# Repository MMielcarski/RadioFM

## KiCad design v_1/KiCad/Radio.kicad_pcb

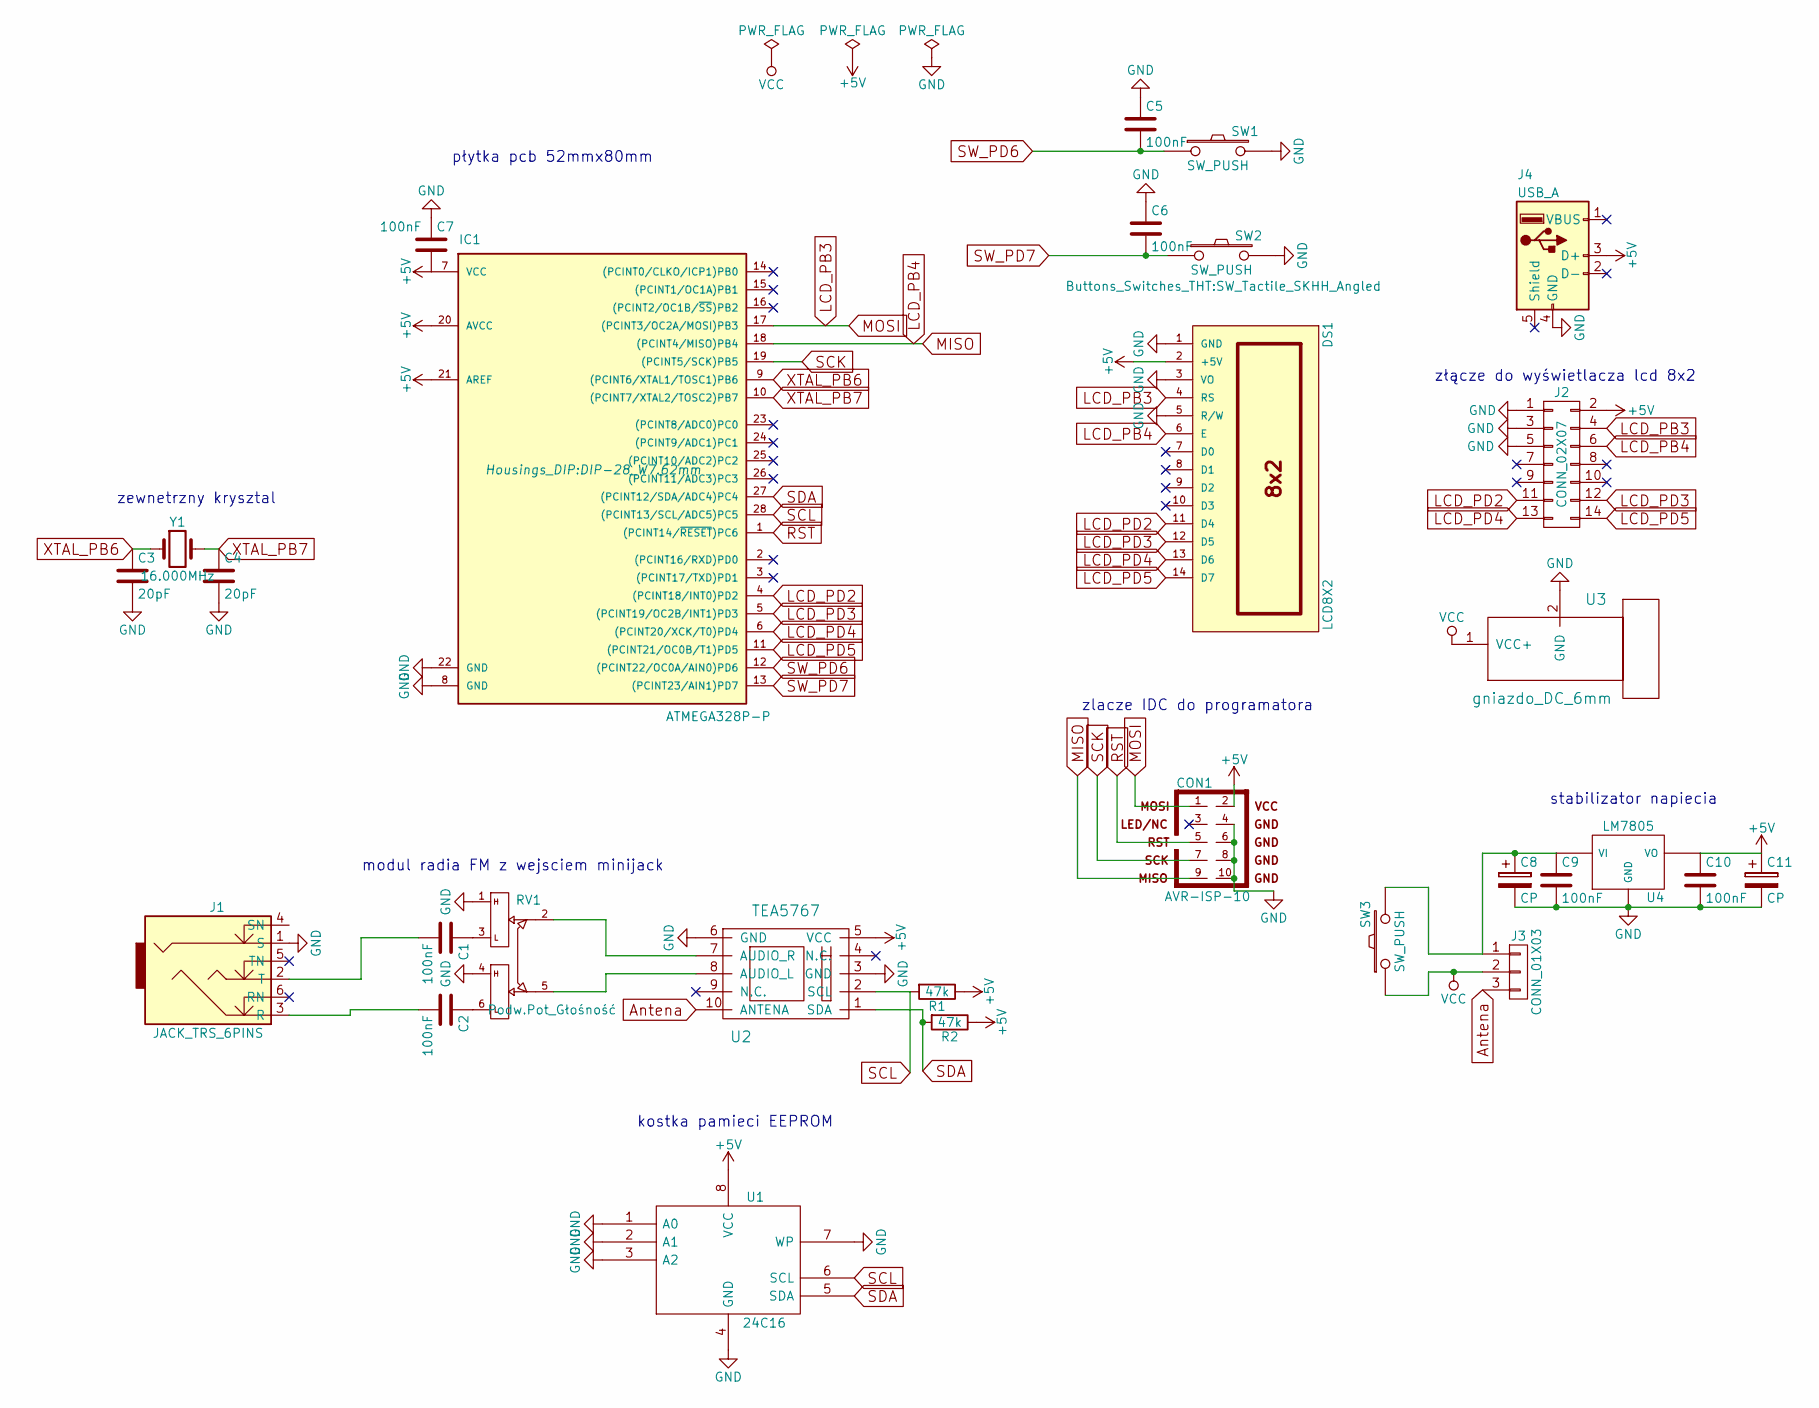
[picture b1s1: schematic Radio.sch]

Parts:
C1, C2, C5, C6, C7, C9, C10: 100nF; CP_Radial_Tantal_D4.5mm_P2.50mm
C3, C4: 20pF; CP_Radial_Tantal_D4.5mm_P2.50mm
C8, C11: CP; CP_Radial_D5.0mm_P2.50mm
CON1: AVR-ISP-10; IDC_Header_Straight_10pins
DS1: LCD8X2
IC1: ATMEGA328P-P; DIP-28_W7.62mm
J1: JACK_TRS_6PINS; Tayda_3.5mm_stereo_TRS_jack_A-853
J2: CONN_02X07; Pin_Header_Straight_2x07_Pitch2.54mm
J3: CONN_01X03; Pin_Header_Straight_1x03_Pitch2.54mm
J4: USB_A
R1, R2: 47k; R_Axial_DIN0204_L3.6mm_D1.6mm_P7.62mm_Horizontal
RV1: Podw.Pot_Głośność; Pin_Header_Straight_2x03_Pitch2.54mm
SW1, SW2, SW3: SW_PUSH; SW_Tactile_SKHH_Angled
U1: 24C16; DIP-8_W7.62mm
U2: TEA5767
U3: gniazdo_DC_6mm
U4: LM7805
Y1: 16.000MHz; Crystal_HC18-U_Vertical

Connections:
+5V: C7.2, C10.1, C11.1, CON1.2, DS1.2 (+5V), IC1.7 (VCC), IC1.20 (AVCC), IC1.21 (AREF), J2.2, J4.3 (D+), R1.1, R2.1, U1.8 (VCC), U2.5 (VCC), U4.3 (VO)
Antena: J3.3, U2.10 (ANTENA)
GND: C3.2, C4.2, C5.1, C6.1, C7.1, C8.2, C9.2, C10.2, C11.2, CON1.4, CON1.6, CON1.8, CON1.10, DS1.1 (GND), DS1.3 (VO), DS1.5 (R/W), IC1.8 (GND), IC1.22 (GND), J1.1 (S), J2.1, J2.3, J2.5, J4.4 (GND), RV1.1, RV1.4, SW1.2, SW2.2, U1.1 (A0), U1.2 (A1), U1.3 (A2), U1.4 (GND), U1.7 (WP), U2.3 (GND), U2.6 (GND), U3.2 (GND), U4.2 (GND)
LCD_PB3: CON1.1, DS1.4 (RS), IC1.17 ((PCINT3/OC2A/MOSI)PB3), J2.4
LCD_PB4: CON1.9, DS1.6 (E), IC1.18 ((PCINT4/MISO)PB4), J2.6
LCD_PD2: DS1.11 (D4), IC1.4 ((PCINT18/INT0)PD2), J2.11
LCD_PD3: DS1.12 (D5), IC1.5 ((PCINT19/OC2B/INT1)PD3), J2.12
LCD_PD4: DS1.13 (D6), IC1.6 ((PCINT20/XCK/T0)PD4), J2.13
LCD_PD5: DS1.14 (D7), IC1.11 ((PCINT21/OC0B/T1)PD5), J2.14
unnamed: C1.1, RV1.3
unnamed: C1.2, J1.2 (T)
unnamed: C2.1, RV1.6
unnamed: C2.2, J1.3 (R)
unnamed: C8.1, C9.1, J3.1, SW3.2, U4.1 (VI)
unnamed: RV1.2, U2.7 (AUDIO_R)
unnamed: RV1.5, U2.8 (AUDIO_L)
RST: CON1.5, IC1.1 ((PCINT14/~RESET~)PC6)
SCK: CON1.7, IC1.19 ((PCINT5/SCK)PB5)
SCL: IC1.28 ((PCINT13/SCL/ADC5)PC5), R1.2, U1.6 (SCL), U2.2 (SCL)
SDA: IC1.27 ((PCINT12/SDA/ADC4)PC4), R2.2, U1.5 (SDA), U2.1 (SDA)
SW_PD6: C5.2, IC1.12 ((PCINT22/OC0A/AIN0)PD6), SW1.1
SW_PD7: C6.2, IC1.13 ((PCINT23/AIN1)PD7), SW2.1
VCC: J3.2, SW3.1, U3.1 (VCC+)
XTAL_PB6: C3.1, IC1.9 ((PCINT6/XTAL1/TOSC1)PB6), Y1.1
XTAL_PB7: C4.1, IC1.10 ((PCINT7/XTAL2/TOSC2)PB7), Y1.2

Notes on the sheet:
płytka pcb 52mmx80mm
złącze do wyświetlacza lcd 8x2
stabilizator napiecia
zlacze IDC do programatora
kostka pamieci EEPROM
modul radia FM z wejsciem minijack
zewnetrzny krysztal

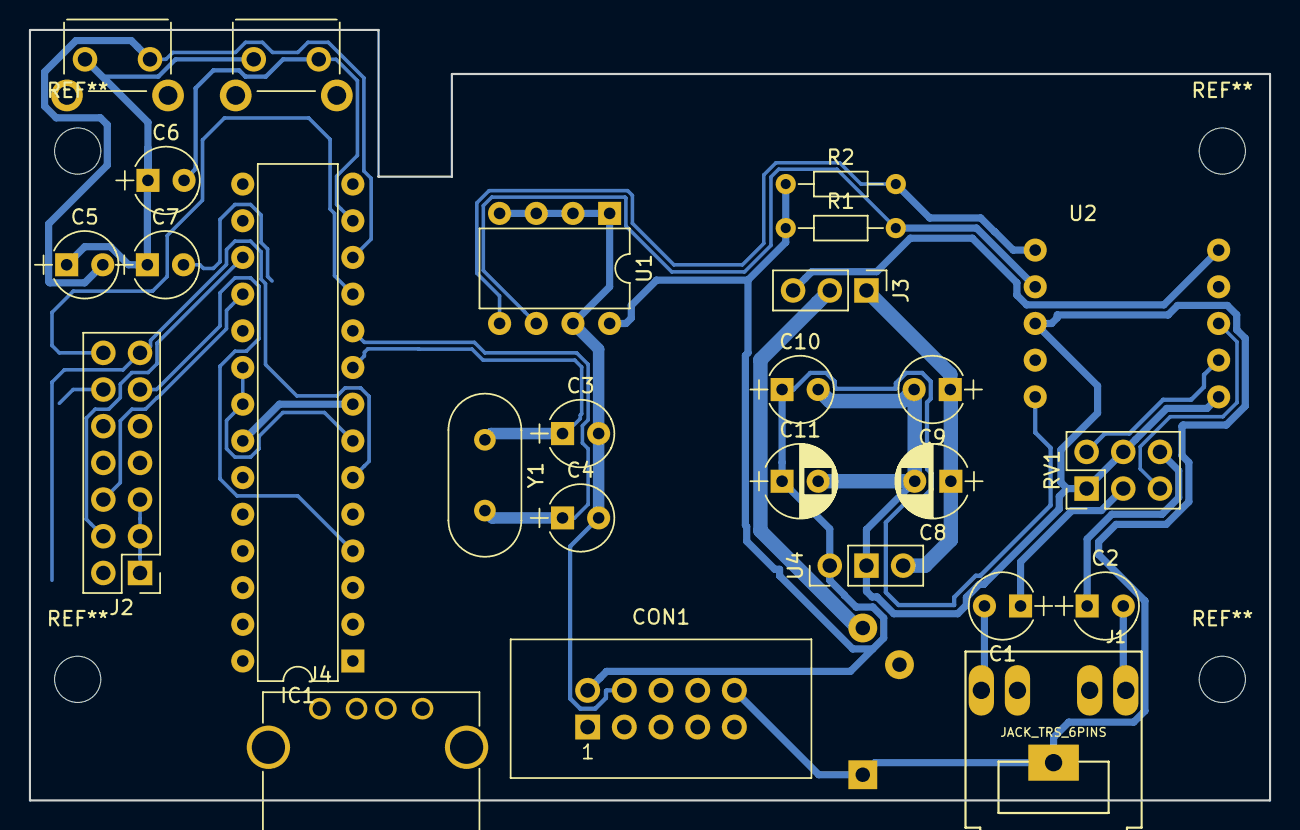
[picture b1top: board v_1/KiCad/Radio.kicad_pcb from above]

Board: 2 copper layers, 85.9 x 53.3 mm, 27 parts (0 on the bottom side), 25 nets.

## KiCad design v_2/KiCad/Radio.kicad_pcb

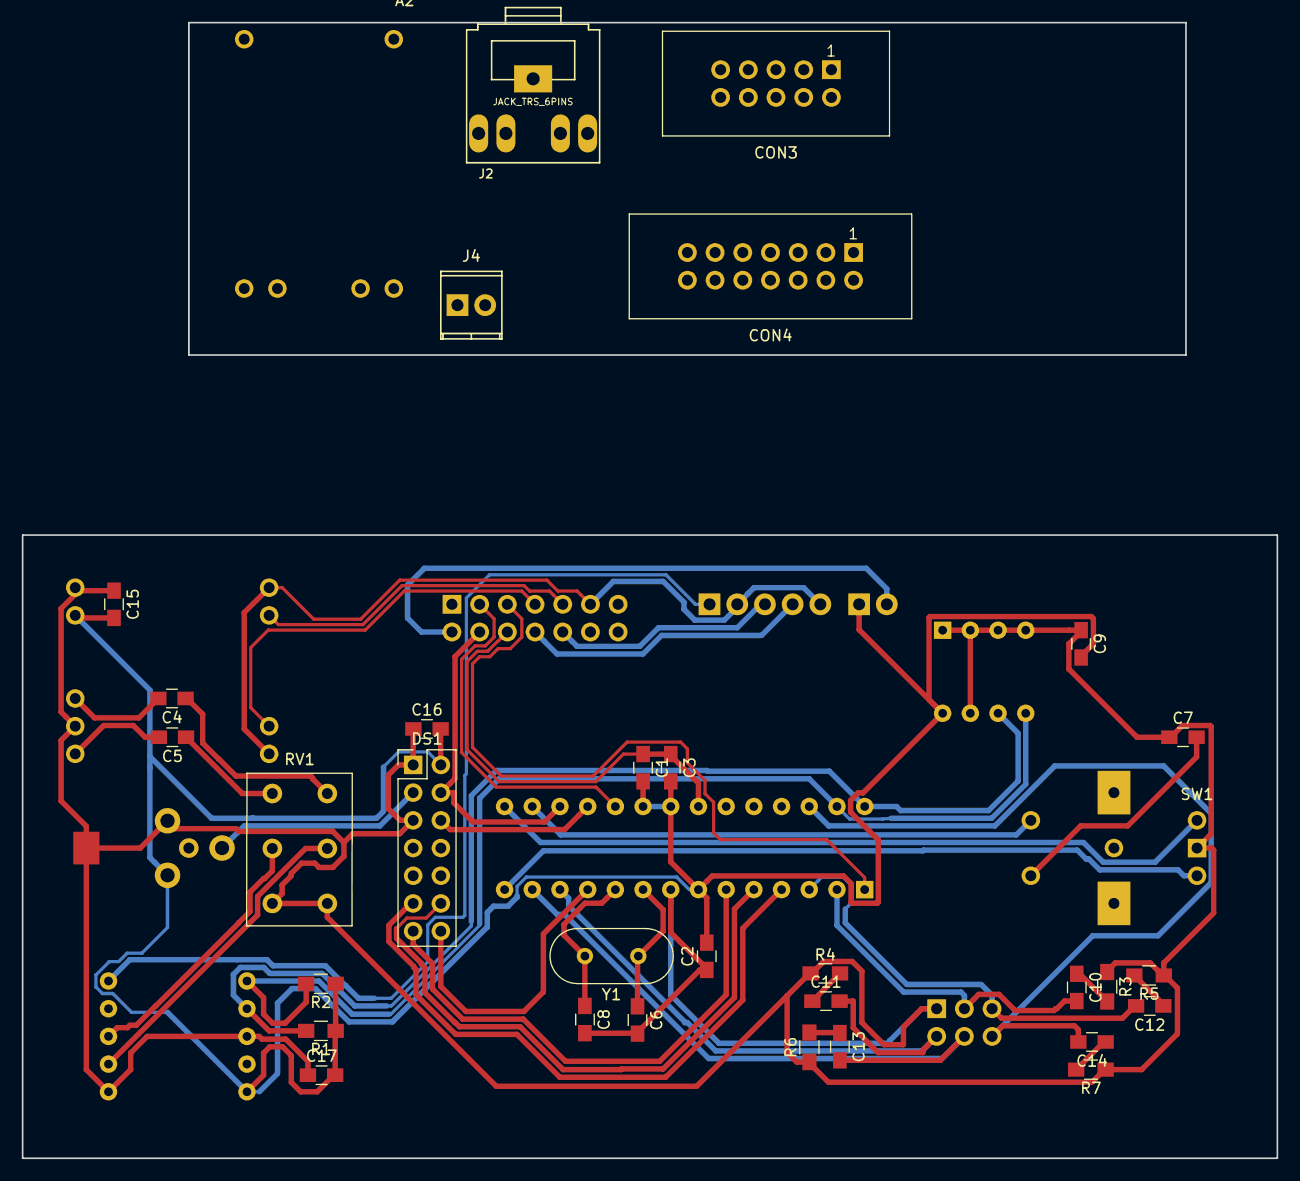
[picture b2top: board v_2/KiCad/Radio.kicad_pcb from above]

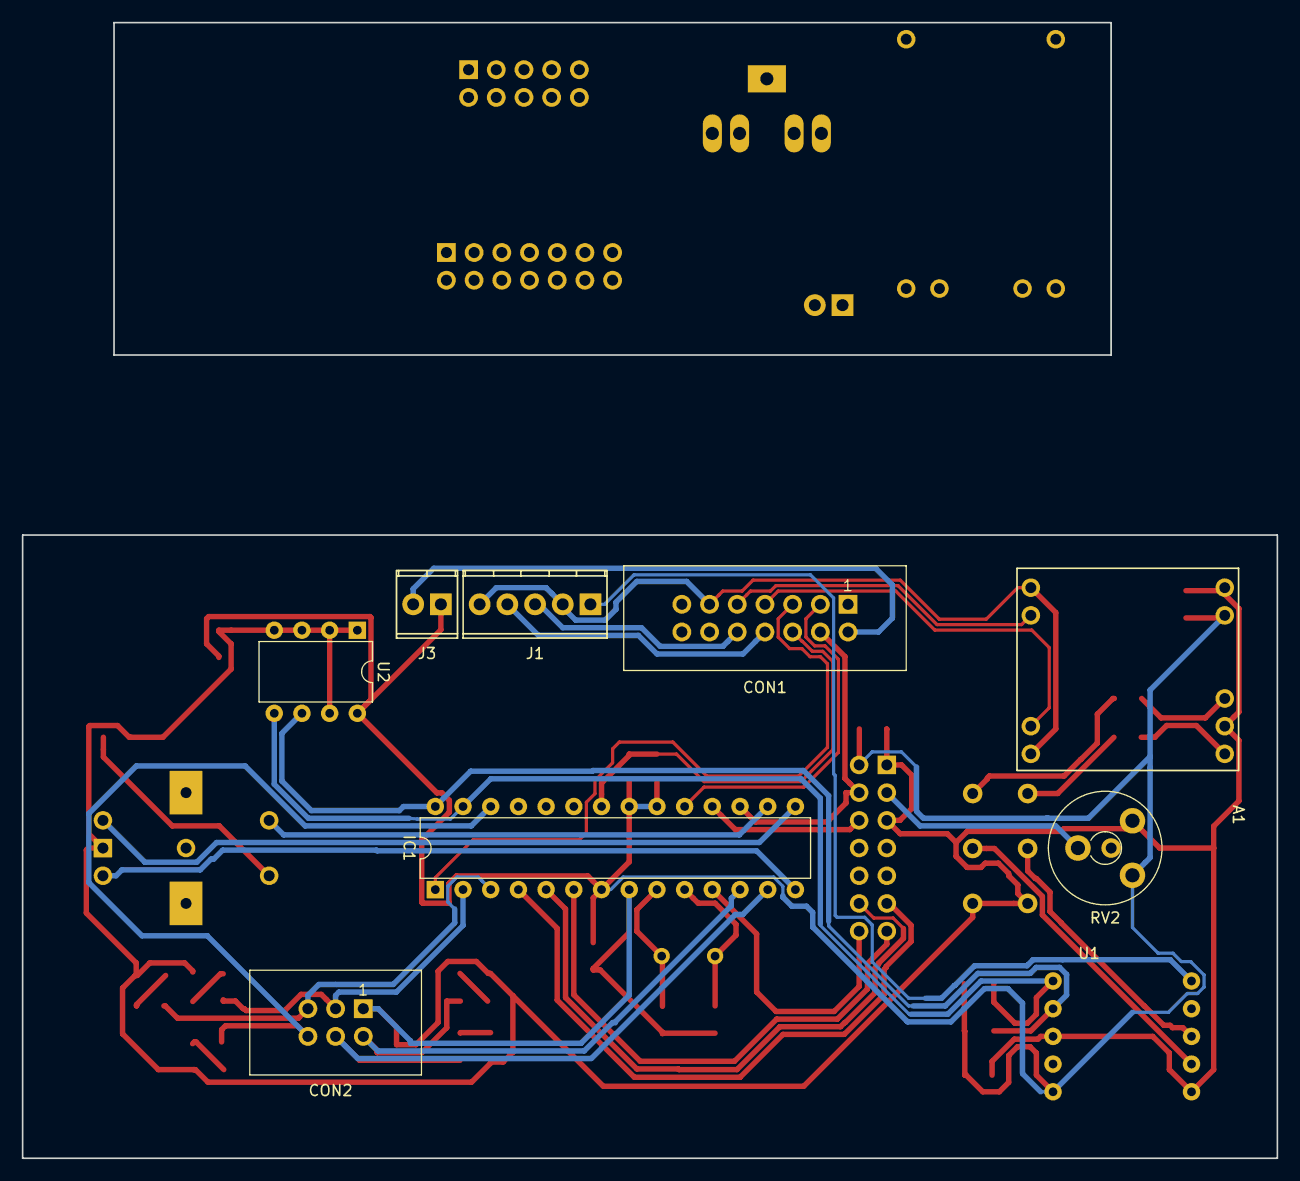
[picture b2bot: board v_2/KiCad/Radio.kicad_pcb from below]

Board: 2 copper layers, 115.1 x 104.1 mm, 42 parts (9 on the bottom side), 49 nets.

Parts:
A1: amp_2x3W_D; PAM8403_module
A2: TP4056; tp_4056_modul_zasilania
C1, C2, C3, C7, C9, C10, C11, C12, C13, C14, C15, C16, C17: 100nF; C_0805_HandSoldering
C4, C5: 1uF; C_0805_HandSoldering
C6, C8: 20pF; C_0805_HandSoldering
CON1, CON4: AVR-ISP-IDC-14; IDC_Header_Straight_14pins
CON2: ISP-IDC-6; IDC_Header_Straight_6pins
CON3: AVR-ISP-10; IDC_Header_Straight_10pins
DS1: LCD8X2; LCD8x2
IC1: ATMEGA328P-P; DIP-28_W7.62mm
J1: Screw_Terminal_1x05; TerminalBlock_Pheonix_MPT-2.54mm_5pol
J2: JACK_TRS_6PINS; Tayda_3.5mm_stereo_TRS_jack_A-853
J3, J4: Screw_Terminal_1x02; TerminalBlock_Pheonix_MPT-2.54mm_2pol
R1, R2: 47k; R_0805_HandSoldering
R3, R4, R5, R6, R7: 100; R_0805_HandSoldering
RV1: Podw.Pot_Głośność; potencjometr_pion
RV2: 10k; Potentiometer_Trimmer_Piher_PT-10v5_Horizontal_Px5.0mm_Py5.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
SW1: Rotary_Encoder_Switch; rotary_encoder
U1: TEA5767
U2: 24C16; DIP-8_W7.62mm
Y1: 16.000MHz; Crystal_HC18-U_Vertical

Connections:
5V_gniazda: A2.6, CON3.2, CON4.2
5V_input: CON1.2, J3.2
+5V: A1.6, C1.2, C2.2, C3.2, C9.2, C15.2, C16.2, C17.2, DS1.2, IC1.7, IC1.20, IC1.21, J3.1, R1.1, R2.1, RV2.3, U1.5, U2.8
Antena: J1.1, U1.10
GND: A1.5, A1.8, A2.3, C1.1, C2.1, C3.1, C6.2, C7.1, C8.2, C9.1, C15.1, C16.1, C17.1, CON1.6, CON2.1, CON3.4, CON3.6, CON3.8, CON3.10, CON4.6, DS1.1, DS1.5, IC1.8, IC1.22, R3.1, R4.1, R5.1, R6.1, R7.1, RV1.1, RV1.4, RV2.1, SW1.2, U1.3, U1.6, U2.1, U2.2, U2.3, U2.4, U2.7
LCD_PB3: CON1.4, CON3.1, CON4.4, DS1.4, IC1.17
LCD_PB4: CON1.1, CON3.9, CON4.1, DS1.6, IC1.18
LCD_PD2: DS1.11, IC1.4
LCD_PD3: DS1.12, IC1.5
LCD_PD4: DS1.13, IC1.6
LCD_PD5: DS1.14, IC1.11
L_IN1: CON1.8, J1.4
L_IN2: CON4.8, J2.4
L_out1: A1.2, CON1.7
L_out2: CON4.7, J2.2
unnamed: A1.7, C4.2
unnamed: A1.9, C5.2
unnamed: C4.1, RV1.3
unnamed: C5.1, RV1.6
unnamed: C7.2, SW1.4
unnamed: C10.1, R3.2
unnamed: C11.1, R4.2
unnamed: C12.1, R5.2
unnamed: C13.1, R6.2
unnamed: C14.1, R7.2
unnamed: DS1.3, RV2.2
unnamed: RV1.2, U1.7
unnamed: RV1.5, U1.8
RST: CON1.5, CON3.5, CON4.5, IC1.1
R_IN1: CON1.10, J1.3
R_IN2: CON4.10, J2.5
R_out1: A1.3, CON1.9
R_out2: CON4.9, J2.3
SCK: CON1.3, CON3.7, CON4.3, IC1.19
SCL: IC1.28, R1.2, U1.2, U2.6
SDA: IC1.27, R2.2, U1.1, U2.5
SW_1: C10.2, CON2.3, IC1.2
SW_2: C12.2, CON2.5, IC1.3
SW_3: C11.2, CON2.2, IC1.12
SW_4: C13.2, CON2.4, IC1.13
SW_5: C14.2, CON2.6, IC1.26
XTAL_PB6: C6.1, IC1.9, Y1.1
XTAL_PB7: C8.1, IC1.10, Y1.2
enkoder_A: IC1.14, SW1.1
enkoder_B: IC1.15, SW1.3
enkoder_switch: IC1.16, SW1.5
gndaudio: A1.1, A1.4, CON1.11, CON4.11, J1.2, J1.5, J2.1
ogniwo+: A2.5, J4.2
ogniwo-: A2.4, J4.1
